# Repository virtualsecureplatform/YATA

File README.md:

This repository is the artifact for the TCHES2026 paper; YATA: Yet Another TFHE Accelerator with Key Compression and Radix-8 NTT

# Directories
- YATA-RTL: RTL codes excluding NDA related things like SRAM IP and PLL. This also contains RTL-level simulations and some Python scripts we used for the design. 
- YATA-PCB: The KiCAD project for the evaluation board.
- YATA-script: Test\&Measurement and making graph scripts, we used to make the evaluation section of our paper. This also contains Equipment.md, the description of the measurement equipment we used.

# LICENSE
RTL is basically licensed under AGPLv3, except for the AsyncQueue, which originated from Rocketchip. 

PCB and scripts are under MIT. 

# Quick Start For Artifact Reviewers
Since reproducing our evaluation entirely requires physical access to our fabricated chip, we only hope to ensure the availability of our artifact. 

## Cloning
Because YATA-RTL includes subprojects, please clone with `--recursive` flag like:

`git clone --recursive https://github.com/virtualsecureplatform/YATA.git`

## YATA-RTL
For 'YATA-RTL', you can find our RTL codes under 'chise/src/main/'. 
To compile our Chisel3 code to Verilog and run tests with Verilator, please install Apptainer or Singularity, then build and run yata-rtl.def. 

## YATA-PCB
You can open the design using KiCAD 9 or later. We also provide the required footprint library under `Library.pretty` and the Gerber file under `jlcpcb`. We believe that if the reviewer can open the design and check the availability of libraries and gerber file, it is enough. 

## YATA-script
Though the main script, `oneshottest.py`, is included,  this requires all the equipment we used to check executability. Hence, we believe just checking the availability is enough. 
`testvectors` includes some data required for measurement using `oneshottest.py`, like input ciphertexts and evaluation keys. 

The important part is that `logs` directory includes our measured data compressed in bzip2. If you installed bzip2 on your machine, running `decompress_pickles.sh` decompresses them.  
After decompression, by running `measured_plot.py`, you can reproduce our Fig. 4 and 6. Because we retouched Figure 6 for readability, you may notice some differences, but this is expected.

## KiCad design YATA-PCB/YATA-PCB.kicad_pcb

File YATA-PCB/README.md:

This PCB is designed using KiCAD 9. 
For assembly, most of the parts can be purchased from DigiKey or Mouser, but SMA connectors and probe sockets are purchased from a local Japanese store. 

https://akizukidenshi.com/catalog/g/g101422/

https://akizukidenshi.com/catalog/g/g115480/

I recommend replacing them with your favorite ones if you plan to reuse this PCB design. 
There is a sense register for measuring current, but we did not use it because the noise seems too high. 

`Library.pretty` includes some libraries we prepared for our PCB, so you have to configure path for them. 

`jlcpcb` includes the Gerber file we used to order our PCB from JLCPCB.

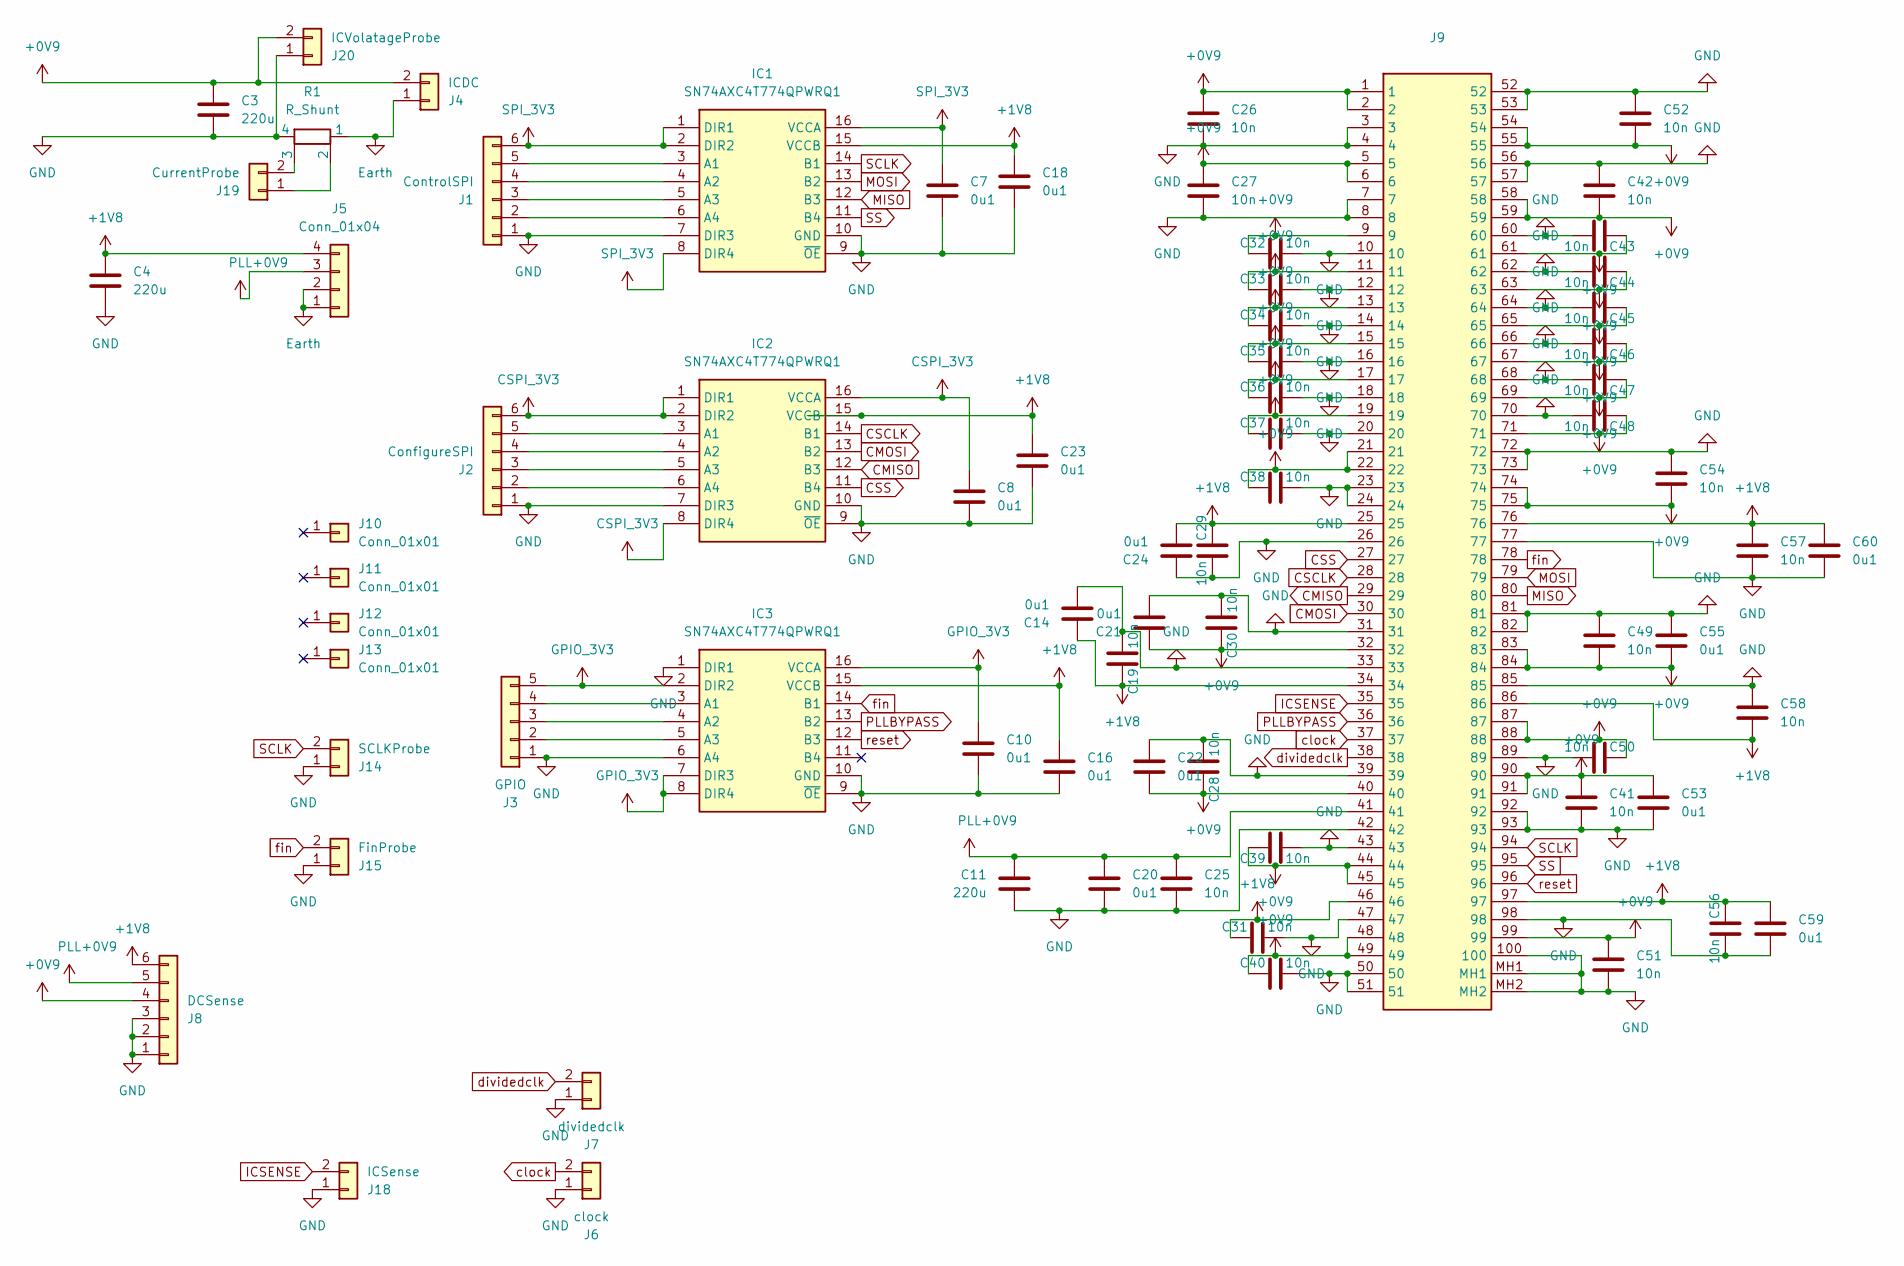
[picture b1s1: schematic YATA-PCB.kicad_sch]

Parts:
C3, C4, C11: 220u; C_1210_3225Metric_Pad1.33x2.70mm_HandSolder
C7, C8, C10, C14, C16, C18, C20, C21, C22, C23, C24, C53, C55, C59, C60: 0u1; C_0402_1005Metric
C19, C25, C26, C27, C28, C29, C30, C31, C32, C33, C34, C35, C36, C37, C38, C39, C40, C41, C42, C43, C44, C45, C46, C47, C48, C49, C50, C51, C52, C54, C56, C57, C58: 10n; C_0201_0603Metric_Pad0.64x0.40mm_HandSolder
IC1, IC2, IC3: SN74AXC4T774QPWRQ1; SOP65P640X120-16N; Manufacturer_Part_Number SN74AXC4T774QPWRQ1; Mouser Part Number 595-74AXC4T774QPWRQ1
J1: ControlSPI; JST_XH_B6B-XH-A_1x06_P2.50mm_Vertical
J2: ConfigureSPI; JST_XH_B6B-XH-A_1x06_P2.50mm_Vertical
J3: GPIO; JST_XH_B5B-XH-A_1x05_P2.50mm_Vertical
J4: ICDC; AMASS_XT30PW-M_1x02_P2.50mm_Horizontal
J5: Conn_01x04; JST_XA_B04B-XASK-1_1x04_P2.50mm_Vertical
J6: clock; Akizuki-SMA
J7: dividedclk; PA013
J8: DCSense; JST_XA_B06B-XASK-1_1x06_P2.50mm_Vertical
J9: IC149-100-014-B5; Manufacturer_Part_Number IC149-100-014-B5; Mouser Part Number 945-IC149-100-014-B5
J10, J11, J12, J13: Conn_01x01; MountingHole_3.2mm_M3_ISO7380_Pad
J14: SCLKProbe; PA013
J15: FinProbe; PA013
J18: ICSense; JST_XA_B02B-XASK-1_1x02_P2.50mm_Vertical
J19: CurrentProbe; PA013
J20: ICVolatageProbe; PA013
R1: R_Shunt; Y14870R01000B9R

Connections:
+0V9: C3.1, C21.1, C22.2, C26.1, C27.1, C28.1, C30.1, C32.1, C33.1, C34.1, C35.1, C36.1, C37.1, C38.1, C39.1, C40.1, C41.1, C42.2, C43.1, C44.1, C45.1, C46.1, C47.1, C48.1, C49.2, C50.1, C51.1, C52.2, C53.1, C54.2, C55.2, J4.2, J8.4, J9.1, J9.2, J9.5, J9.6, J9.9, J9.11, J9.13, J9.15, J9.17, J9.19, J9.21, J9.22, J9.32, J9.40, J9.44, J9.45, J9.48, J9.49, J9.54, J9.55, J9.58, J9.59, J9.61, J9.63, J9.65, J9.67, J9.69, J9.71, J9.74, J9.75, J9.83, J9.84, J9.87, J9.88, J9.90, J9.91, J9.99, J20.2
+1V8: C4.1, C14.1, C16.1, C18.1, C19.1, C23.1, C24.2, C29.1, C31.1, C56.1, C57.1, C58.2, C59.1, C60.1, IC1.15 (VCCB), IC2.15 (VCCB), IC3.15 (VCCB), J5.4, J8.6, J9.25, J9.34, J9.46, J9.76, J9.86, J9.97
CMISO: IC2.12 (B3), J9.29
CMOSI: IC2.13 (B2), J9.30
CSCLK: IC2.14 (B1), J9.28
CSPI_3V3: C8.1, IC2.1 (DIR1), IC2.2 (DIR2), IC2.8 (DIR4), IC2.16 (VCCA), J2.6
CSS: IC2.11 (B4), J9.27
Earth: J4.1, J5.1, J5.2, R1.1
GND: C3.2, C4.2, C7.2, C8.2, C10.2, C11.2, C14.2, C16.2, C18.2, C19.2, C20.2, C21.2, C22.1, C23.2, C24.1, C25.2, C26.2, C27.2, C28.2, C29.2, C30.2, C31.2, C32.2, C33.2, C34.2, C35.2, C36.2, C37.2, C38.2, C39.2, C40.2, C41.2, C42.1, C43.2, C44.2, C45.2, C46.2, C47.2, C48.2, C49.1, C50.2, C51.2, C52.1, C53.2, C54.1, C55.1, C56.2, C57.2, C58.1, C59.2, C60.2, IC1.7 (DIR3), IC1.9 (~OE), IC1.10 (GND), IC2.7 (DIR3), IC2.9 (~OE), IC2.10 (GND), IC3.1 (DIR1), IC3.6 (A4), IC3.9 (~OE), IC3.10 (GND), J1.1, J2.1, J3.1, J6.1, J7.1, J8.1, J8.2, J8.3, J9.3, J9.4, J9.7, J9.8, J9.10, J9.12, J9.14, J9.16, J9.18, J9.20, J9.23, J9.24, J9.26, J9.31, J9.33, J9.39, J9.42, J9.43, J9.47, J9.50, J9.51, J9.52, J9.53, J9.56, J9.57, J9.60, J9.62, J9.64, J9.66, J9.68, J9.70, J9.72, J9.73, J9.77, J9.81, J9.82, J9.85, J9.89, J9.92, J9.93, J9.98, J9.100, J9.MH1, J9.MH2, J14.1, J15.1, J18.1, J20.1, R1.4
GPIO_3V3: C10.1, IC3.2 (DIR2), IC3.7 (DIR3), IC3.8 (DIR4), IC3.16 (VCCA), J3.5
ICSENSE: J9.35, J18.2
MISO: IC1.12 (B3), J9.80
MOSI: IC1.13 (B2), J9.79
unnamed: IC1.3 (A1), J1.5
unnamed: IC1.4 (A2), J1.4
unnamed: IC1.5 (A3), J1.3
unnamed: IC1.6 (A4), J1.2
unnamed: IC2.3 (A1), J2.5
unnamed: IC2.4 (A2), J2.4
unnamed: IC2.5 (A3), J2.3
unnamed: IC2.6 (A4), J2.2
unnamed: IC3.3 (A1), J3.4
unnamed: IC3.4 (A2), J3.3
unnamed: IC3.5 (A3), J3.2
unnamed: J19.1, R1.2
unnamed: J19.2, R1.3
PLL+0V9: C11.1, C20.1, C25.1, J5.3, J8.5, J9.41
PLLBYPASS: IC3.13 (B2), J9.36
SCLK: IC1.14 (B1), J9.94, J14.2
SPI_3V3: C7.1, IC1.1 (DIR1), IC1.2 (DIR2), IC1.8 (DIR4), IC1.16 (VCCA), J1.6
SS: IC1.11 (B4), J9.95
clock: J6.2, J9.37
dividedclk: J7.2, J9.38
fin: IC3.14 (B1), J9.78, J15.2
reset: IC3.12 (B3), J9.96

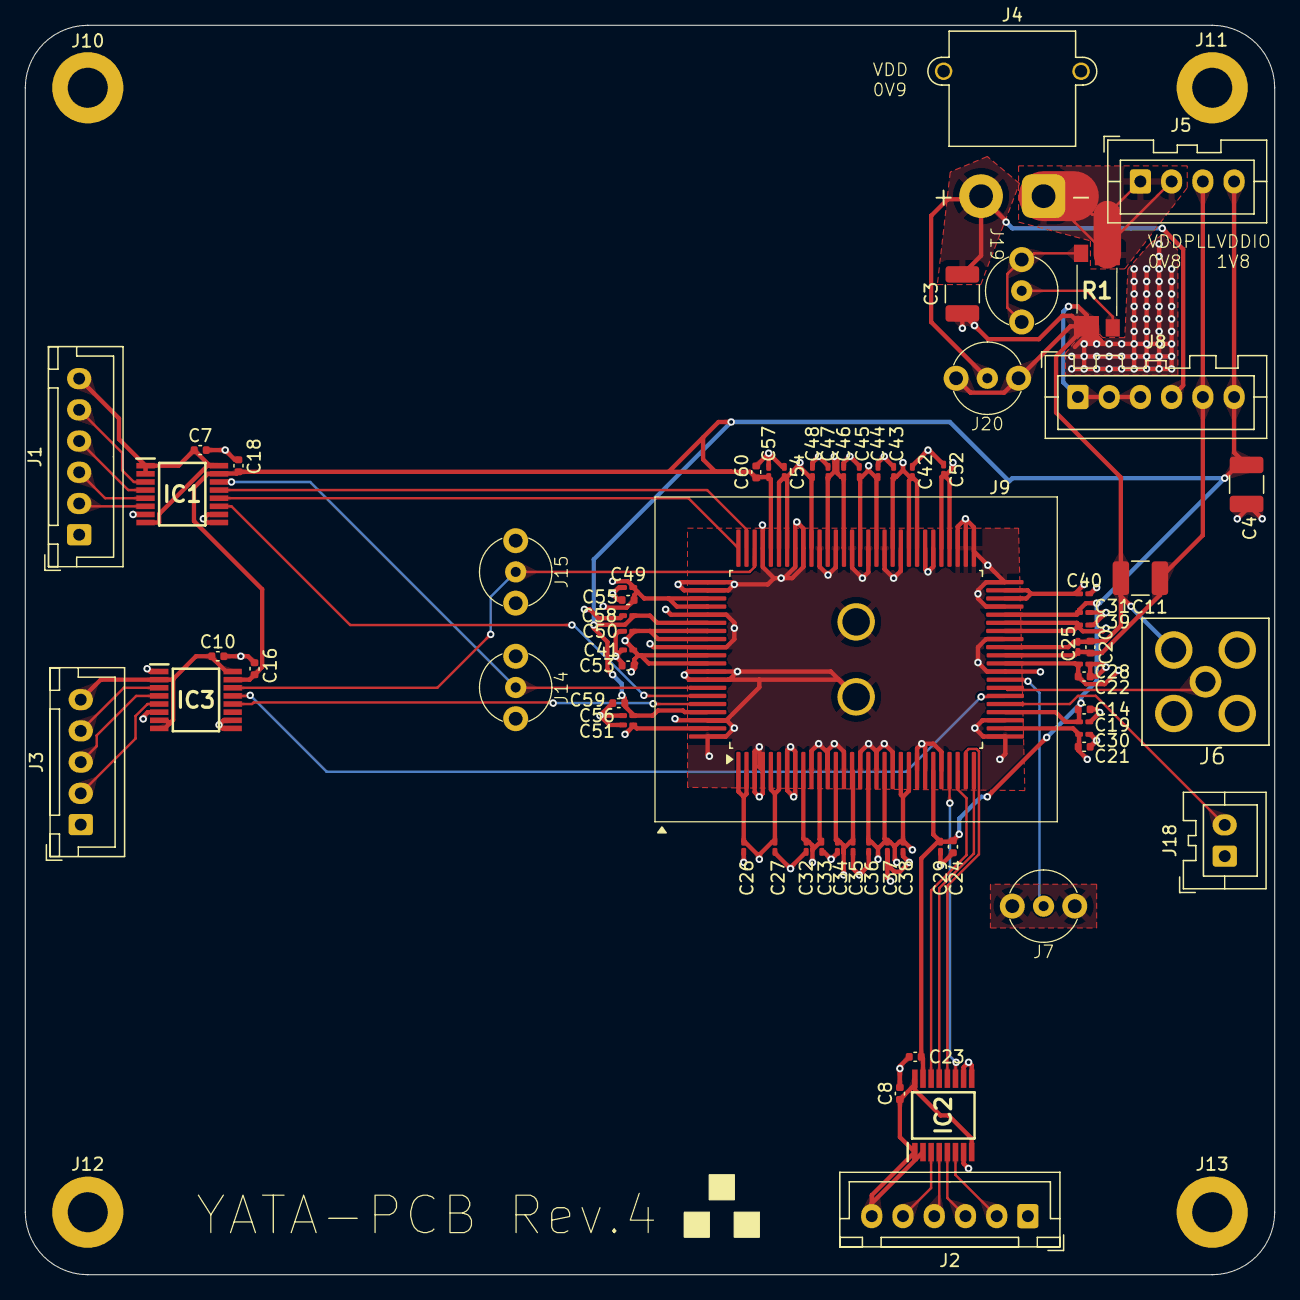
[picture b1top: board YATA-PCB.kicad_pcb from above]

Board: 4 copper layers, 100.0 x 100.0 mm, 73 parts (0 on the bottom side), 35 nets.

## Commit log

2025-10-24 Add the version prepared for review
2025-10-25 Add README for PCB
2025-10-28 fix build.sbt
2025-10-29 remove unnecessary option
2025-10-29 Fix readme and add def file
2025-10-29 Add measured data
2025-10-29 clarify YATA-script description
2025-10-29 Enhance README with script and data information
    Updated README to clarify script details and data locations.
2025-10-29 Format README.md for better readability
2025-10-30 Fix typo in README.md regarding sense resistor
2025-10-30 Fix typos and enhance README content
    Correct spelling errors and improve clarity in the README.
2025-10-30 Fix typos and enhance clarity in README.md
    Corrected typos and improved phrasing in README.
2025-10-30 Update README.md for clarity and corrections
    Corrected typos and improved clarity in the README.
2025-10-30 Update README with clearer instructions and details
    Clarified instructions for reproducing figures and added details about the test vectors directory.
2025-11-20 Add cloning instructions to README
    Added instructions for cloning the repository with subprojects.
2025-11-20 Insert newline for readability
2025-11-20 Added requirements.txt
2025-12-18 Fix typo
2025-12-18 Update README with package details and corrections
    Clarified package descriptions and fixed grammatical errors in README.
